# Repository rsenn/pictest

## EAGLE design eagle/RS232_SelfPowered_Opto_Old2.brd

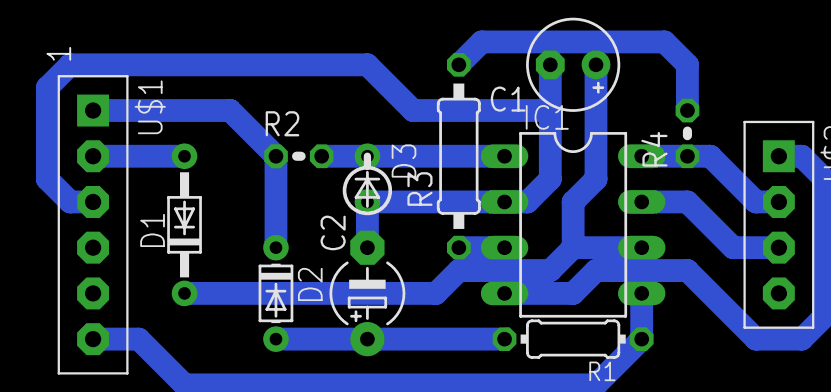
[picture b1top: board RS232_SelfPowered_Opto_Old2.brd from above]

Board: 2 copper layers, 12 parts (0 on the bottom side), 12 nets.

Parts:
C1: 47u; E2,5-5
C2: 47u; E5-4
D1: 1N914; DO34-7
D2: 1N914; DO34-5
D3: 1N914; DO35-2_54
IC1: ACPL-827; DIL08
R1: 680Ω; 0204/7
R2, R4: 1kΩ; 0204V
R3: 470Ω; 0207/10
U$1: COMPORT-6PIN-6P; CONN-6P
U$2: PIC-UART-4P; CONN-4P

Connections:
+5V: R3.2, R4.2
DGND: IC1.7, U$2.3
GND: C1.-, C2.-, D3.A, IC1.2, U$1.3
unnamed: D1.A, U$1.2
unnamed: C1.+, D1.C, IC1.6
unnamed: IC1.3, R3.1
unnamed: IC1.4, U$2.1
unnamed: IC1.8, R4.1, U$2.2
unnamed: D3.C, IC1.1, R2.2
unnamed: C2.+, D2.A, R1.2
unnamed: IC1.5, R1.1, U$1.6
unnamed: D2.C, R2.1, U$1.1

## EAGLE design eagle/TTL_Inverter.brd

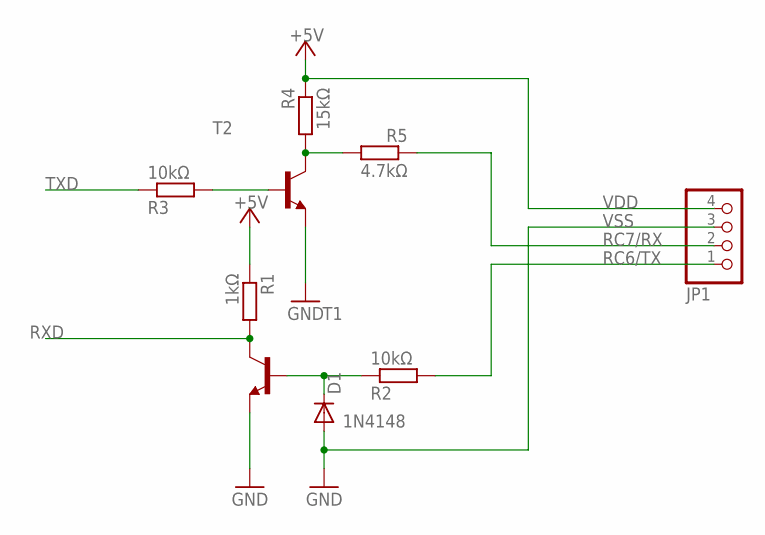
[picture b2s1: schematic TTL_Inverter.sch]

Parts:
D1: 1N4148; DO35-7
JP1: PINHD-1X4; 1X04
R1: 1kΩ; 0207/2V
R2: 10kΩ; 0207/7
R3: 10kΩ; 0207/10
R4: 15kΩ; 0207/10
R5: 4.7kΩ; 0207/2V
T1, T2: BC547-NPN-TO92-CBE; TO92-CBE

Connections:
GND: T1.E, T2.E
unnamed: R3.2, T2.B
unnamed: R4.2, R5.2, T2.C
unnamed: D1.C, R2.1, T1.B
RC6/TX: JP1.1, R2.2
RC7/RX: JP1.2, R5.1
RXD: R1.2, T1.C
TXD: R3.1
VDD: JP1.4, R1.1, R4.1
VSS: D1.A, JP1.3

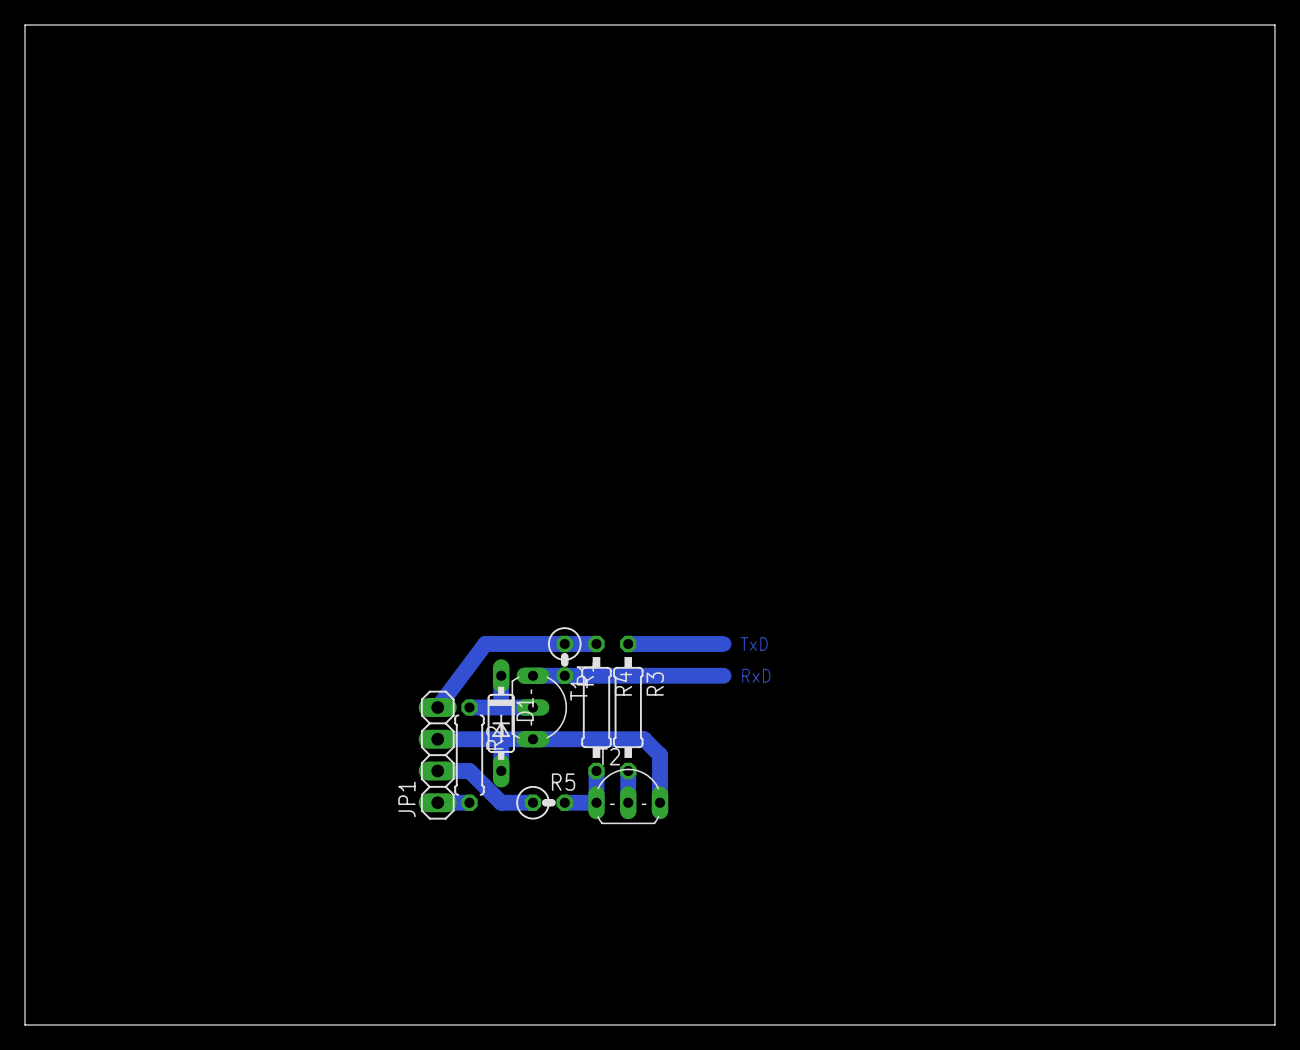
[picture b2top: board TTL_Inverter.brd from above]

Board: 2 copper layers, 100.0 x 80.0 mm, 9 parts (0 on the bottom side), 9 nets.

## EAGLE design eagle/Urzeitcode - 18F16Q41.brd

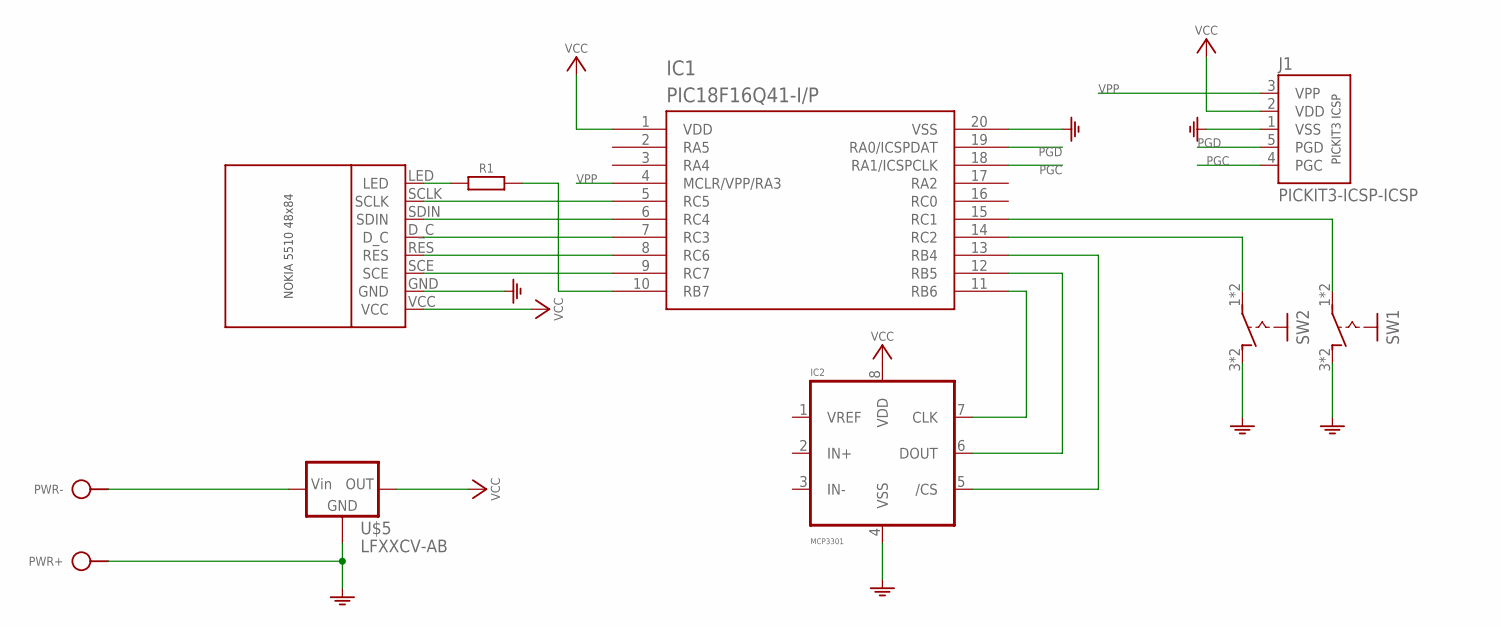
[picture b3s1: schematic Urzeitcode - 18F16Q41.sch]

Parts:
IC1: PIC18F16Q41-I/P; DIL20-3/V
IC2: MCP3301; DIL08
J1: PICKIT3-ICSP-ICSP; PIC-ICSP
PWR: SPAD+-+-; SPAD+-
R1: R-H0204/15-V; 0204/15-V
SW1, SW2: PB-1P-1T2P1T; PB-2P1T
U$2: NOKIA-5510-48X84-MODULE; MOD-LCD5110
U$5: LFXXCV-AB; TO220AB

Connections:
GND: IC1.20 (VSS), IC2.4 (VSS), J1.1 (VSS), PWR.2, SW1.3 (S), SW1.4 (S), SW2.3 (S), SW2.4 (S), U$2.GND, U$5.2 (GND)
unnamed: IC1.5 (RC5), U$2.SCLK
unnamed: IC1.6 (RC4), U$2.SDIN
unnamed: IC1.7 (RC3), U$2.D_C
unnamed: IC1.8 (RC6), U$2.RES
unnamed: IC1.9 (RC7), U$2.SCE
unnamed: R1.1, U$2.LED
unnamed: IC1.10 (RB7), R1.2
unnamed: IC1.13 (RB4), IC2.5 (/CS)
unnamed: IC1.12 (RB5), IC2.6 (DOUT)
unnamed: IC1.11 (RB6), IC2.7 (CLK)
unnamed: IC1.14 (RC2), SW2.1, SW2.2
unnamed: IC1.15 (RC1), SW1.1, SW1.2
unnamed: PWR.1, U$5.1 (VIN)
PGC: IC1.18 (RA1/ICSPCLK), J1.4 (PGC)
PGD: IC1.19 (RA0/ICSPDAT), J1.5 (PGD)
VCC: IC1.1 (VDD), IC2.8 (VDD), J1.2 (VDD), U$2.VCC, U$5.3 (VOUT)
VPP: IC1.4 (MCLR/VPP/RA3), J1.3 (VPP)

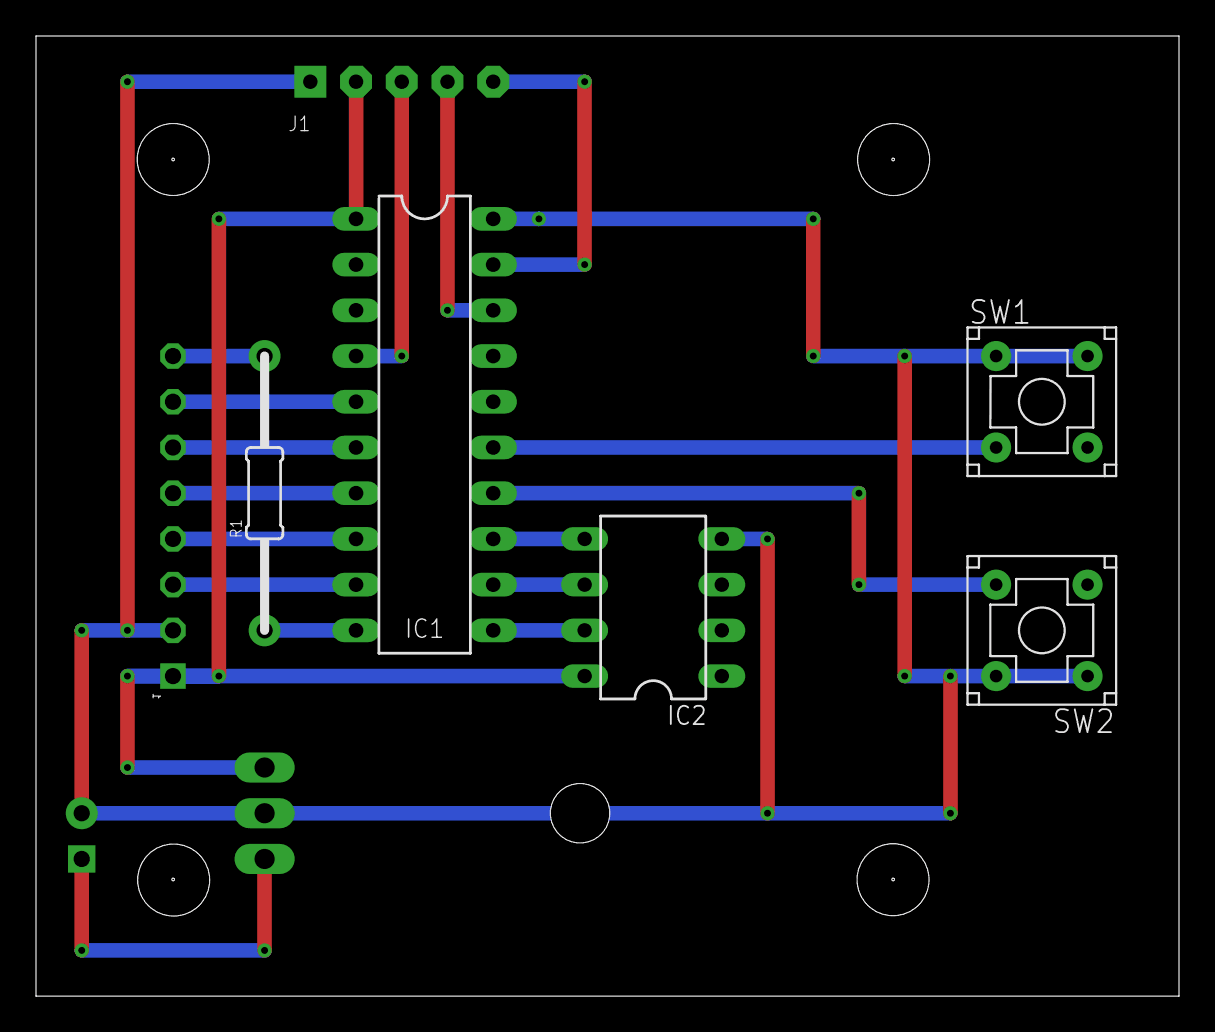
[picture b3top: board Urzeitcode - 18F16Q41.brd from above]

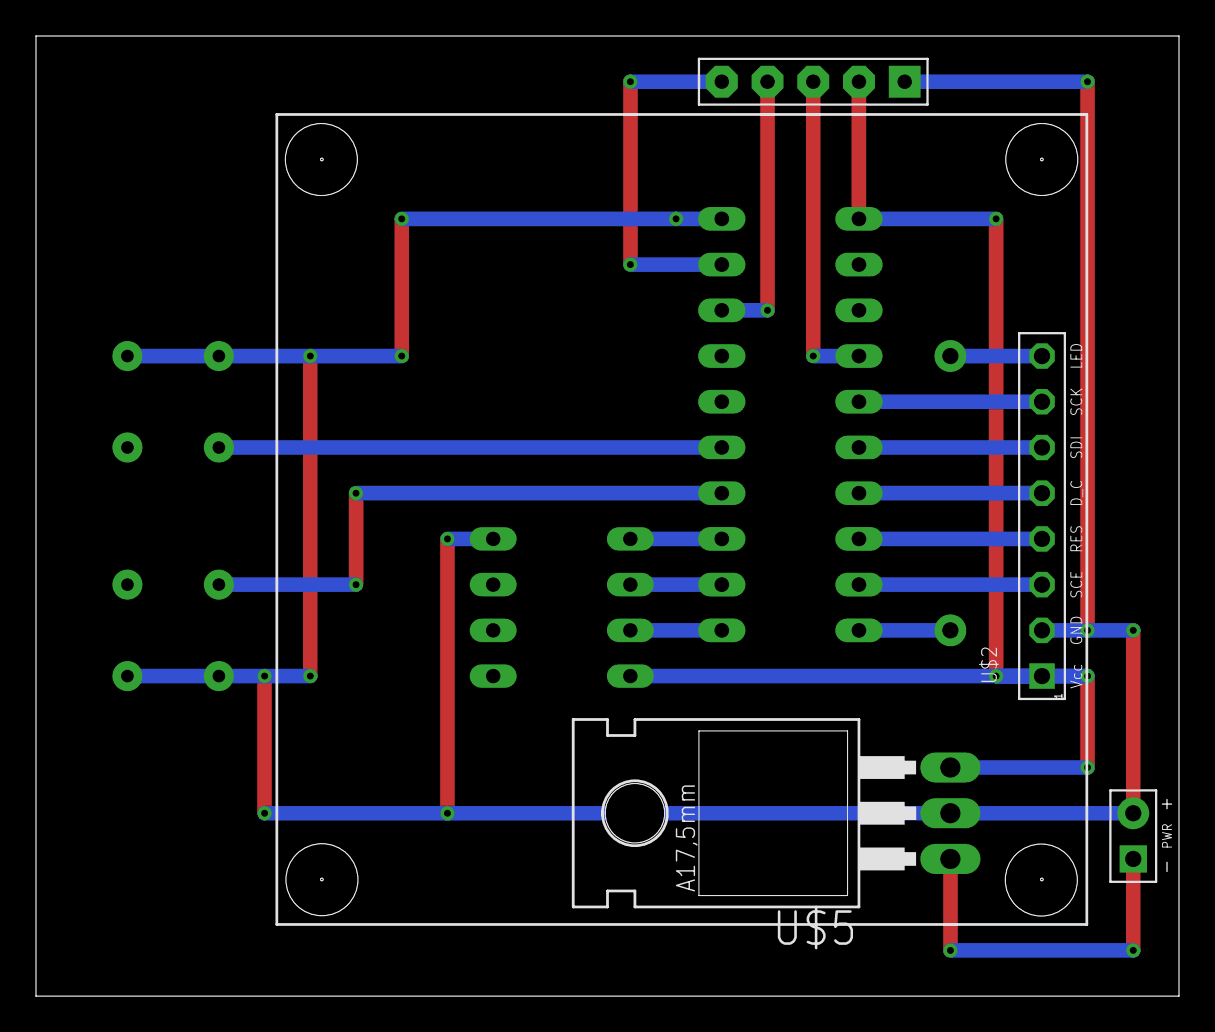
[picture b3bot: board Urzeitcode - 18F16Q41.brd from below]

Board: 2 copper layers, 63.5 x 53.3 mm, 9 parts (3 on the bottom side), 18 nets.

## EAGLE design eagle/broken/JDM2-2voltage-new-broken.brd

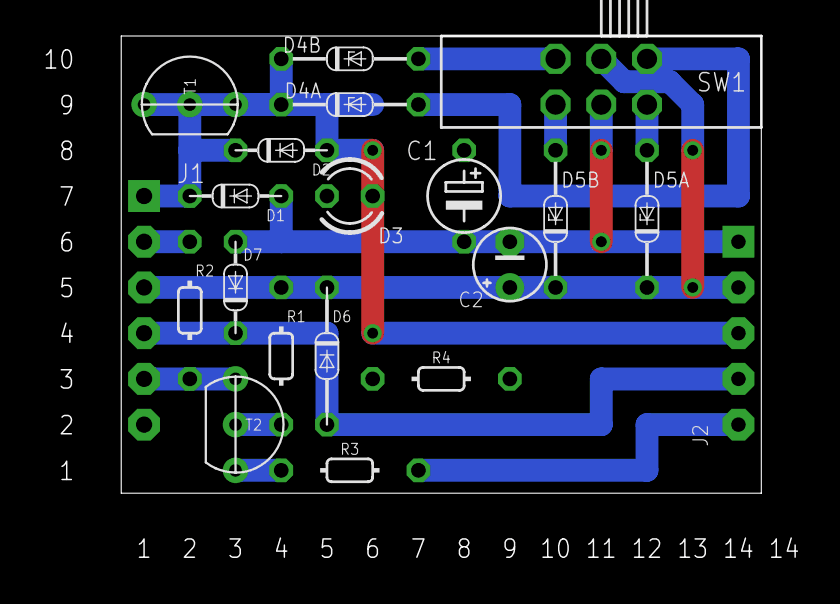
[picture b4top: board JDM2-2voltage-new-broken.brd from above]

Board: 2 copper layers, 35.6 x 25.4 mm, 20 parts (0 on the bottom side), 16 nets.

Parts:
C1: 100uF; E5-4
C2: 22uF; E2,5-4
D1, D2: 1N4148; DO34-5
D3: LED (red); LED3MM
D4A: Z=5.1V; DO34Z7
D4B: Z=8.1V; DO34Z7
D5A: Z=3.3V; DO34Z7V
D5B: Z=5.1V; DO34Z7V
D6: 1N4148; DO34-7V
D7: 1N4148; DO34-5V
J1: COMPORT-6PIN; RS232-6PIN
J2: PIC-ICSPICSP; PIC-ICSP
R1: 10k; 0202/7-V
R2: 1.5k; 0202/7-V
R3: 100; 0202/7
R4: 3.3k; 0202/7
SW1: SL-SW-2P-2T-S; SLSW-2P2T-H
T1, T2: BC547; TO92-CBE

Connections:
/MCLR: D2.A, J2.3, R4.2, T1.E
CLK: D6.A, D7.C, J1.4, J2.4
CTS: J1.5, R2.1, T2.C
DATA: R3.2, T2.E
GND: C1.-, C2.-, D1.A, D3.K, D7.A, J2.1, SW1.5
unnamed: R1.1, T2.B
unnamed: D5A.A, SW1.4
unnamed: D5B.A, SW1.6
unnamed: D4A.A, SW1.1
unnamed: D3.A, R4.1
unnamed: D4B.A, SW1.3
unnamed: J1.2, R2.2
PGD: J2.5, R3.1
TXD: D1.C, D2.C, J1.1, T1.B
VCC: C2.+, D5A.C, D5B.C, D6.C, J1.3, J2.2, R1.2, SW1.2
VPP: C1.+, D4A.C, D4B.C, T1.C

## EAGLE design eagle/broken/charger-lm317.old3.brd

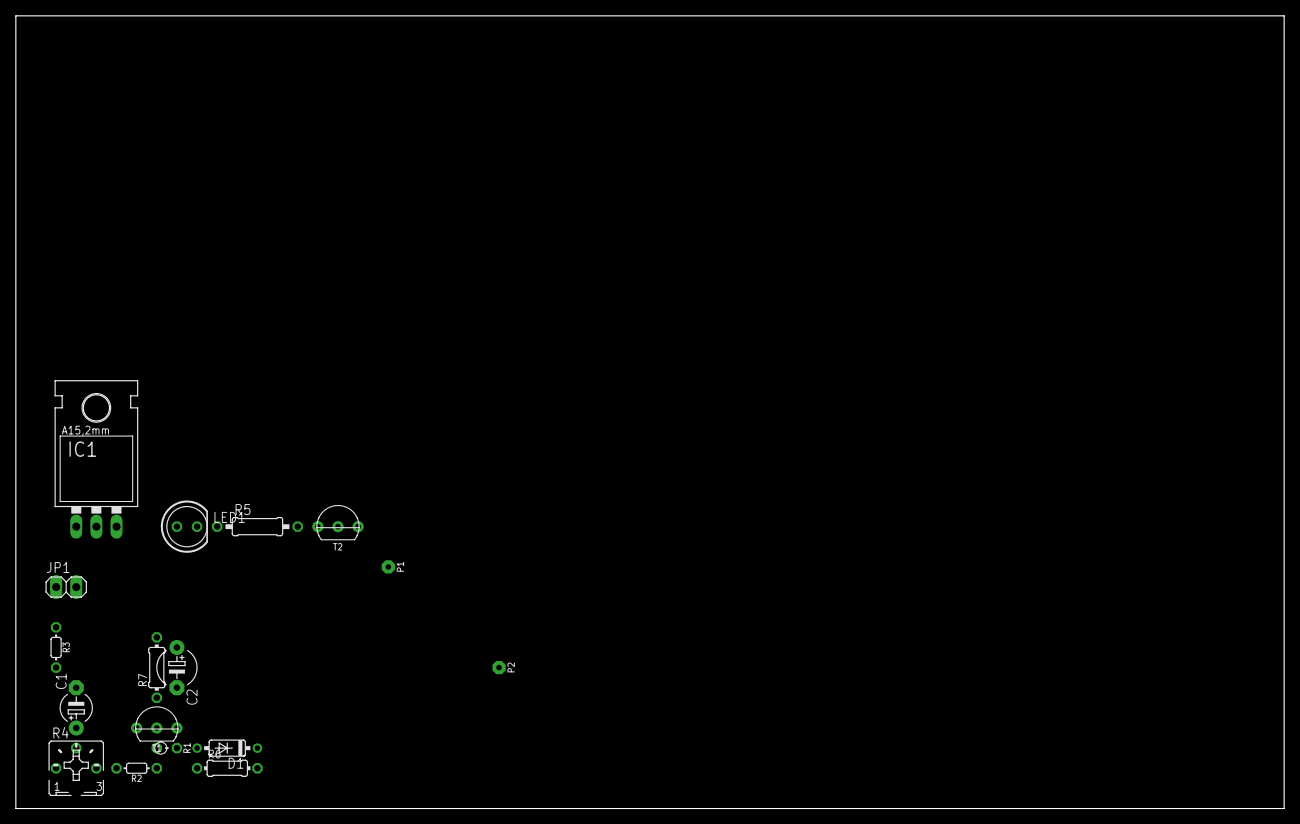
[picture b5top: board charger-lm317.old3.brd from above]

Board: 2 copper layers, 160.0 x 100.0 mm, 17 parts (0 on the bottom side), 11 nets, no tracks yet.

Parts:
C1: E5-4
C2: E5-5
D1: 1N4148-7; DO35-7
IC1: 317TL
JP1: 1X02
LED1: LED5MM
P1, P2: SPAD
R1: 0202/2V
R2, R3: 2.2k; 0202/5
R4: B25P
R5: 0207/10
R6, R7: 0204/7
T1, T2: BC547CBE; TO92-CBE

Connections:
unnamed: C1.+, IC1.1, R4.S, T1.C
unnamed: IC1.2, JP1.1, R3.1
unnamed: C1.-, C2.-, D1.A, R1.2, R6.1, T1.E
unnamed: R2.2, R4.E
unnamed: JP1.2, R1.1, R2.1, R7.1, T1.B
unnamed: D1.C, P2.1, R6.2, T2.E
unnamed: R5.2, T2.C
unnamed: LED1.K, R5.1
unnamed: C2.+, IC1.3, LED1.A, P1.1
unnamed: R3.2, R4.A
unnamed: R7.2, T2.B
